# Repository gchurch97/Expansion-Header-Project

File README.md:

# Expansion-Header-Project

DEO GPIO_1 to Breadboard adapter.

Measures 2inch by 3inch landscape.

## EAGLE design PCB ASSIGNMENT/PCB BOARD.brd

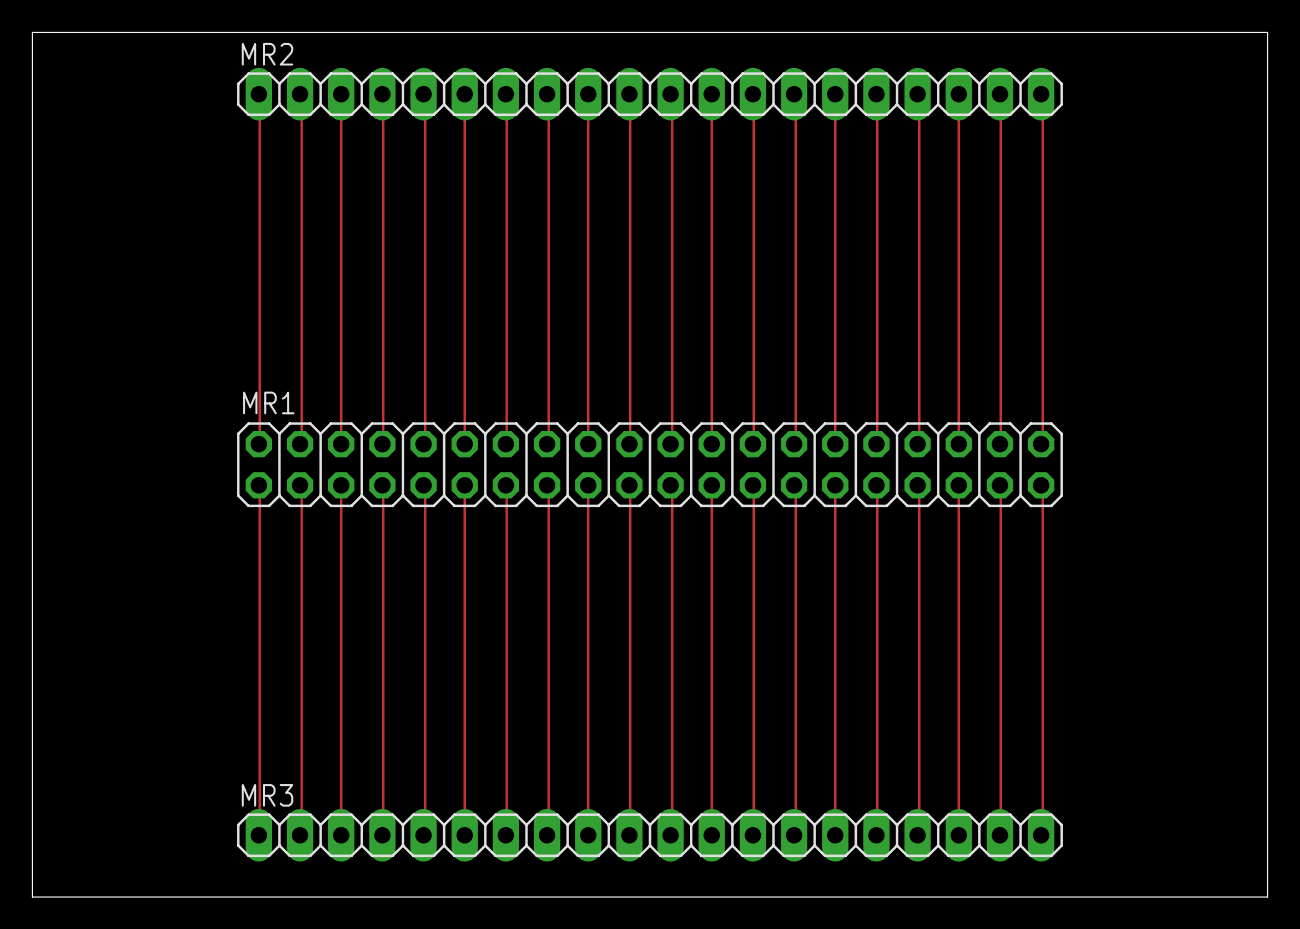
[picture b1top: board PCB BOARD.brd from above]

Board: 2 copper layers, 76.2 x 53.3 mm, 3 parts (0 on the bottom side), 40 nets.

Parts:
MR1: 2X20
MR2, MR3: 1X20

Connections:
GND: MR1.21, MR3.11
unnamed: MR1.1, MR3.1
unnamed: MR1.9, MR3.5
unnamed: MR1.3, MR3.2
unnamed: MR1.5, MR3.3
unnamed: MR1.7, MR3.4
unnamed: MR1.11, MR3.6
unnamed: MR1.13, MR3.7
unnamed: MR1.15, MR3.8
unnamed: MR1.17, MR3.9
unnamed: MR1.19, MR3.10
unnamed: MR1.2, MR2.1
unnamed: MR1.25, MR3.13
unnamed: MR1.27, MR3.14
unnamed: MR1.29, MR3.15
unnamed: MR1.31, MR3.16
unnamed: MR1.33, MR3.17
unnamed: MR1.35, MR3.18
unnamed: MR1.37, MR3.19
unnamed: MR1.39, MR3.20
unnamed: MR1.40, MR2.20
unnamed: MR1.38, MR2.19
unnamed: MR1.36, MR2.18
unnamed: MR1.34, MR2.17
unnamed: MR1.32, MR2.16
unnamed: MR1.30, MR2.15
unnamed: MR1.28, MR2.14
unnamed: MR1.26, MR2.13
unnamed: MR1.24, MR2.12
unnamed: MR1.22, MR2.11
unnamed: MR1.20, MR2.10
unnamed: MR1.18, MR2.9
unnamed: MR1.16, MR2.8
unnamed: MR1.14, MR2.7
unnamed: MR1.12, MR2.6
unnamed: MR1.10, MR2.5
unnamed: MR1.8, MR2.4
unnamed: MR1.6, MR2.3
unnamed: MR1.4, MR2.2
VCC: MR1.23, MR3.12

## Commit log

2018-04-25 Rename ShematicPCB.txt to BillOFMaterial.txt
